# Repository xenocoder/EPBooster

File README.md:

Schematic and Board for EP Booster.

Version 1.0 - 11/21/2013
First finished version
Uploaded to OSHPark for order

Version 1.1 11/23/2013
Changed wire widths to 0.024
Replaced all components from G-M to madbean due to really small pads and drill sizes. This increased drill sizes on parts from 0.7mm to 1mm. Also changed pad size from auto to 1.89mm.
Uploaded to OSHPark.

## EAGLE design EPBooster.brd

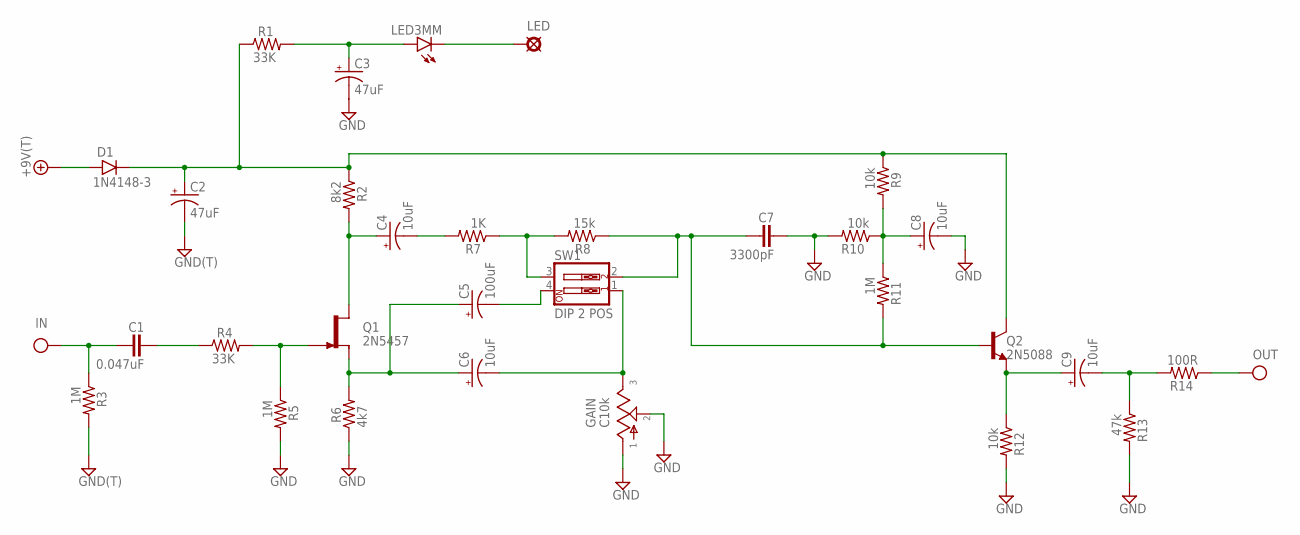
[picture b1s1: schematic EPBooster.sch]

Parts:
+9/18V: +9V(T); SQUARE
C1: 0.047uF; 072X025
C2, C3: 47uF; 050_020_1
C4, C6, C8, C9: 10uF; 050_020_1
C5: 100uF; 063_025
C7: 3300pF; 072X025
D1: 1N4148-3; DO35-3
G: GND(T); SQUARE
GAIN: C10k; POT
GND: GND(T); SQUARE
IN: IN(T); SQUARE
LED: PAD; SQUARE
LED3MM: 3MM; LED3MM
OUT: OUT(T); SQUARE
Q1: 2N5457; TO92-
Q2: 2N5088; TO92-
R1, R4: 33K; R0204/2
R2: 8k2; R0204/2
R3, R5, R11: 1M; R0204/2
R6: 4k7; R0204/2
R7: 1K; R0204/2
R8: 15k; R0204/2
R9, R10, R12: 10k; R0204/2
R13: 47k; R0204/2
R14: 100R; R0204/2
SW1: DIP 2 POS; EDG-02

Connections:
+9V: +9/18V.1, D1.A
GND: C2.-, C3.-, C7.2, C8.-, G.1, GAIN.1, GAIN.2, GND.1, R3.2, R5.2, R6.1, R10.2, R12.2, R13.2
IN: C1.1, IN.1, R3.1
unnamed: C3.+, LED3MM.A, R1.2
unnamed: C2.+, D1.C, Q2.1 (C), R1.1, R2.1, R9.1
unnamed: C1.2, R4.1
unnamed: Q1.1 (G), R4.2, R5.1
unnamed: C4.+, Q1.3 (D), R2.2
unnamed: C5.+, C6.+, Q1.2 (S), R6.2
unnamed: C4.-, R7.2
unnamed: C5.-, SW1.4
unnamed: C9.+, Q2.3 (E), R12.1
unnamed: C6.-, GAIN.3, SW1.1
unnamed: R7.1, R8.2, SW1.3
unnamed: C9.-, R13.1, R14.2
unnamed: C8.+, R9.2, R10.1, R11.1
unnamed: LED.1, LED3MM.K (C)
unnamed: C7.1, Q2.2 (B), R8.1, R11.2, SW1.2
OUT: OUT.1, R14.1

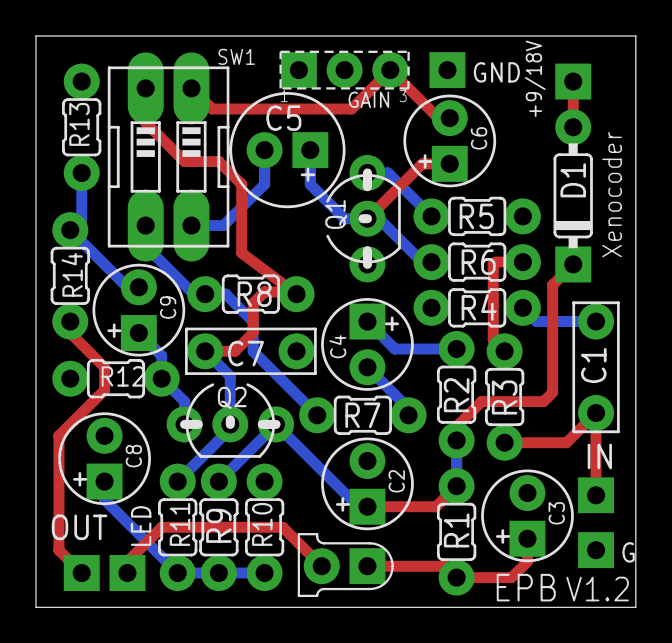
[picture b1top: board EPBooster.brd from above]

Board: 2 copper layers, 33.3 x 31.7 mm, 35 parts (0 on the bottom side), 19 nets.

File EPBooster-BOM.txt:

Partlist

Exported from EPBooster-V1.1.brd at 4/9/14 8:42 PM

EAGLE Version 6.5.0 Copyright (c) 1988-2013 CadSoft

Assembly variant: 

Part     Value          Package   Library          Position (inch)       Orientation

+9/18V   +9V(T)         SQUARE    mb_supply        (1.9 1)               R0
C1       0.047uF        075X040   mb_caps-chicklet (1.575 0.725)         R270
C2       47uF           063_025   mb_caps-electro  (0.8 0.175)           R90
C3       47uF           063_025   mb_caps-electro  (1.775 0.175)         R180
C4       10uF           063_025   mb_caps-electro  (0.815 0.465)         R0
C5       100uF          080_035_1 mb_caps-electro  (1.175 0.5)           R90
C6       10uF           063_025   mb_caps-electro  (1.325 0.75)          R90
C7       3300pF         075X040   mb_caps-chicklet (0.515 0.78)          R270
C8       10uF           063_025   mb_caps-electro  (0.15 0.15)           R180
C9       10uF           063_025   mb_caps-electro  (0.15 0.425)          R180
D1       1N4148-3       DO35-3    mb_diodes        (1.9 0.725)           R90
G        GND(T)         SQUARE    mb_supply        (0.075 1)             R0
GAIN     C10k           POT       mb_pots          (1.4 0.975)           R180
IN       IN(T)          SQUARE    mb_supply        (1.75 1)              R0
LED      3mm            SQUARE    mb_supply        (1.95 0.075)          R0
OUT      OUT(T)         SQUARE    mb_supply        (0.225 1)             R0
Q1       2N5457         TO92-     mb_trans         (1.075 0.225)         R90
Q2       2N5088         TO92-     mb_trans         (0.45 0.45)           R0
R1       33K            R0207/3   mb_resistors     (1.785 0.37)          R0
R2       8k2            R0207/3   mb_resistors     (1.425 0.1)           R180
R3       1M             R0207/3   mb_resistors     (1.75 0.725)          R270
R4       33K            R0207/3   mb_resistors     (1.53 0.47)           R180
R5       1M             R0207/3   mb_resistors     (1.4 0.305)           R0
R6       4k7            R0207/3   mb_resistors     (1.4 0.205)           R180
R7       1K             R0207/3   mb_resistors     (0.94 0.695)          R0
R8       15k            R0207/3   mb_resistors     (0.65 0.775)          R270
R9       10k            R0207/3   mb_resistors     (0.475 0.075)         R180
R10      10k            R0207/3   mb_resistors     (0.475 0.3)           R0
R11      1M             R0207/3   mb_resistors     (0.475 0.19)          R0
R12      10k            R0207/3   mb_resistors     (0.35 0.75)           R90
R13      47k            R0207/3   mb_resistors     (0.1 0.75)            R90
R14      100R           R0207/3   mb_resistors     (0.225 0.75)          R270
SW1      DIP 2 POS      EDG-02    mb_dip switch    (0.96 0.885)          R90

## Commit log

2015-10-08 Files to make v1.0
2015-10-08 Changed files for v1.1
2015-10-08 New Board and Schematic for v1.2
2015-10-08 Changed board and schematic for v1.3
